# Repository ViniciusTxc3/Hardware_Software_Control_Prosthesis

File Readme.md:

Trabalho desenvolvido no BioLab - UFU para o controle de uma prótese robótica. Nele consta o desenvolvimento do software de controle em um microcontrolador DSPIC em c/c++ e os design das placas de controle PCB.

# Esse trabalho teve a colaboração direta de:
* Vinicius Teixeira da Costa, 
* Professor Alcimar Barbosa Soares, 
* Eber Lawrence Gouveia, 
* Arthur Coeolho

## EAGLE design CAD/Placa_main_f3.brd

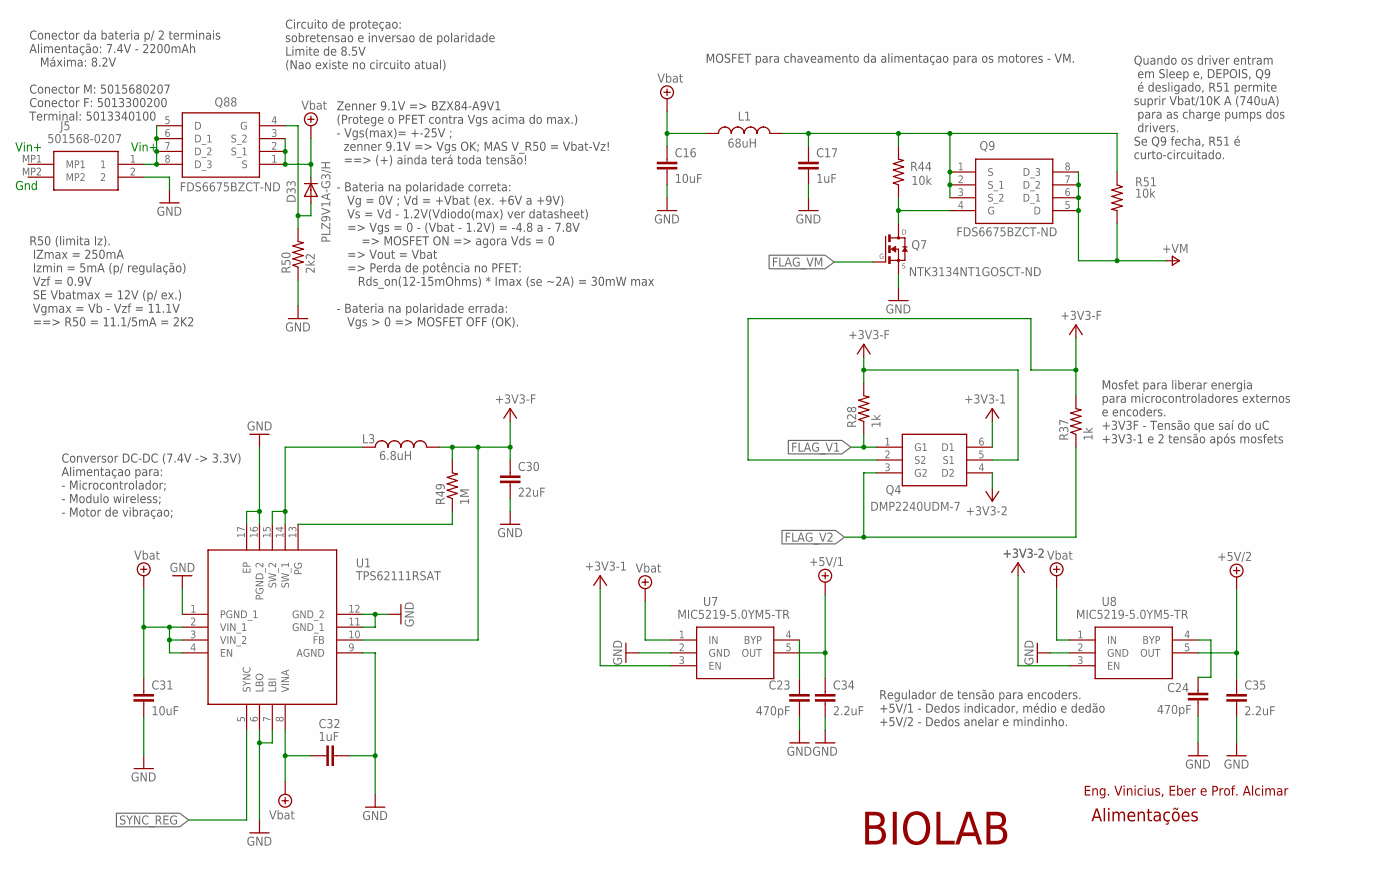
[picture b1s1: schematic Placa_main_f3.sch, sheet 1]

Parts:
C16, C31: 10uF; C0805K
C17, C32: 1uF; C0402K
C23, C24: 470pF; C0402K
C30: 22uF; C0805K
C34, C35: 2.2uF; C0402K
D33: PLZ9V1A-G3/H; MINIMELF
J5: 501568-0207; 5015680207
L1: 68uH; L2825P
L3: 6.8uH; L2825P
Q4: DMP2240UDM-7; SOT95P285X140-6N
Q7: NTK3134NT1GOSCT-ND; SOT23
Q9, Q88: FDS6675BZCT-ND; SOIC127P600X175-8N
R28, R37: 1k; R0402
R44, R51: 10k; R0402
R49: 1M; R0402
R50: 2k2; R0402
U1: TPS62111RSAT; QFN65P400X400X100-17N
U7, U8: MIC5219-5.0YM5-TR; SOT95P280X145-5N

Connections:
+3V3: C30.1, L3.2, Q4.2 (S2), Q4.5 (S1), R28.2, R37.2, R49.2, U1.10 (FB), U7.3 (EN); also elsewhere on the board
+3V3-1: Q4.6 (D1); also elsewhere on the board
+3V3-2: Q4.4 (D2), U8.3 (EN); also elsewhere on the board
+5V/1: C34.1, U7.5 (OUT); also elsewhere on the board
+5V/2: C35.1, U8.5 (OUT); also elsewhere on the board
FLAG_V1: Q4.1 (G1), R28.1; also elsewhere on the board
FLAG_V2: Q4.3 (G2), R37.1; also elsewhere on the board
FLAG_VM: Q7.1 (G); also elsewhere on the board
GND: C16.2, C17.2, C23.2, C24.2, C30.2, C31.2, C32.2, C34.2, C35.2, J5.2, Q7.2 (S), R50.1, U1.1 (PGND_1), U1.6 (LBO), U1.7 (LBI), U1.9 (AGND), U1.11 (GND_1), U1.12 (GND_2), U1.16 (PGND_2), U1.17 (EP), U7.2 (GND), U8.2 (GND); also elsewhere on the board
unnamed: C17.1, L1.2, Q9.1 (S), Q9.2 (S_1), Q9.3 (S_2), R44.2, R51.1
unnamed: Q7.3 (D), Q9.4 (G), R44.1
unnamed: C24.1, U8.4 (BYP)
unnamed: C23.1, U7.4 (BYP)
unnamed: R49.1, U1.13 (PG)
unnamed: L3.1, U1.14 (SW_1), U1.15 (SW_2)
unnamed: D33.A, Q88.4 (G), R50.2
SYNC_REG: U1.5 (SYNC); also elsewhere on the board
V+: Q9.5 (D), Q9.6 (D_1), Q9.7 (D_2), Q9.8 (D_3), R51.2; also elsewhere on the board
VBAT: C16.1, C31.1, C32.1, D33.C, L1.1, Q88.1 (S), Q88.2 (S_1), Q88.3 (S_2), U1.2 (VIN_1), U1.3 (VIN_2), U1.4 (EN), U1.8 (VINA), U7.1 (IN), U8.1 (IN); also elsewhere on the board
VIN+: J5.1, Q88.5 (D), Q88.6 (D_1), Q88.7 (D_2), Q88.8 (D_3)

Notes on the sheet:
Conector da bateria p/ 2 terminais Alimentação: 7.4V - 2200mAh Máxima: 8.2V Conector M: 5015680207 Conector F: 5013300200 Terminal: 5013340100
Circuito de proteçao: sobretensao e inversao de polaridade Limite de 8.5V (Nao existe no circuito atual)
Conversor DC-DC (7.4V -> 3.3V) Alimentaçao para: - Microcontrolador; - Modulo wireless; - Motor de vibraçao;
Regulador de tensão para encoders. +5V/1 - Dedos indicador, médio e dedão +5V/2 - Dedos anelar e mindinho.
MOSFET para chaveamento da alimentaçao para os motores - VM.
BIOLAB
Eng. Vinicius, Eber e Prof. Alcimar
Mosfet para liberar energia para microcontroladores externos e encoders. +3V3F - Tensão que saí do uC +3V3-1 e 2 tensão após mosfets
Alimentações
R50 (limita Iz). IZmax = 250mA Izmin = 5mA (p/ regulação) Vzf = 0.9V SE Vbatmax = 12V (p/ ex.) Vgmax = Vb - Vzf = 11.1V ==> R50 = 11.1/5mA = 2K2
Zenner 9.1V => BZX84-A9V1 (Protege o PFET contra Vgs acima do max.) - Vgs(max)= +-25V ; zenner 9.1V => Vgs OK; MAS V_R50 = Vbat-Vz! ==> (+) ainda terá toda tensão! - Bateria na polaridade correta: Vg = 0V ; Vd = +Vbat (ex. +6V a +9V) Vs = Vd - 1.2V(Vdiodo(max) ver datasheet) => Vgs = 0 - (Vbat - 1.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
Quando os driver entram em Sleep e, DEPOIS, Q9 é desligado, R51 permite suprir Vbat/10K A (740uA) para as charge pumps dos drivers. Se Q9 fecha, R51 é curto-circuitado.
Vin+
Gnd

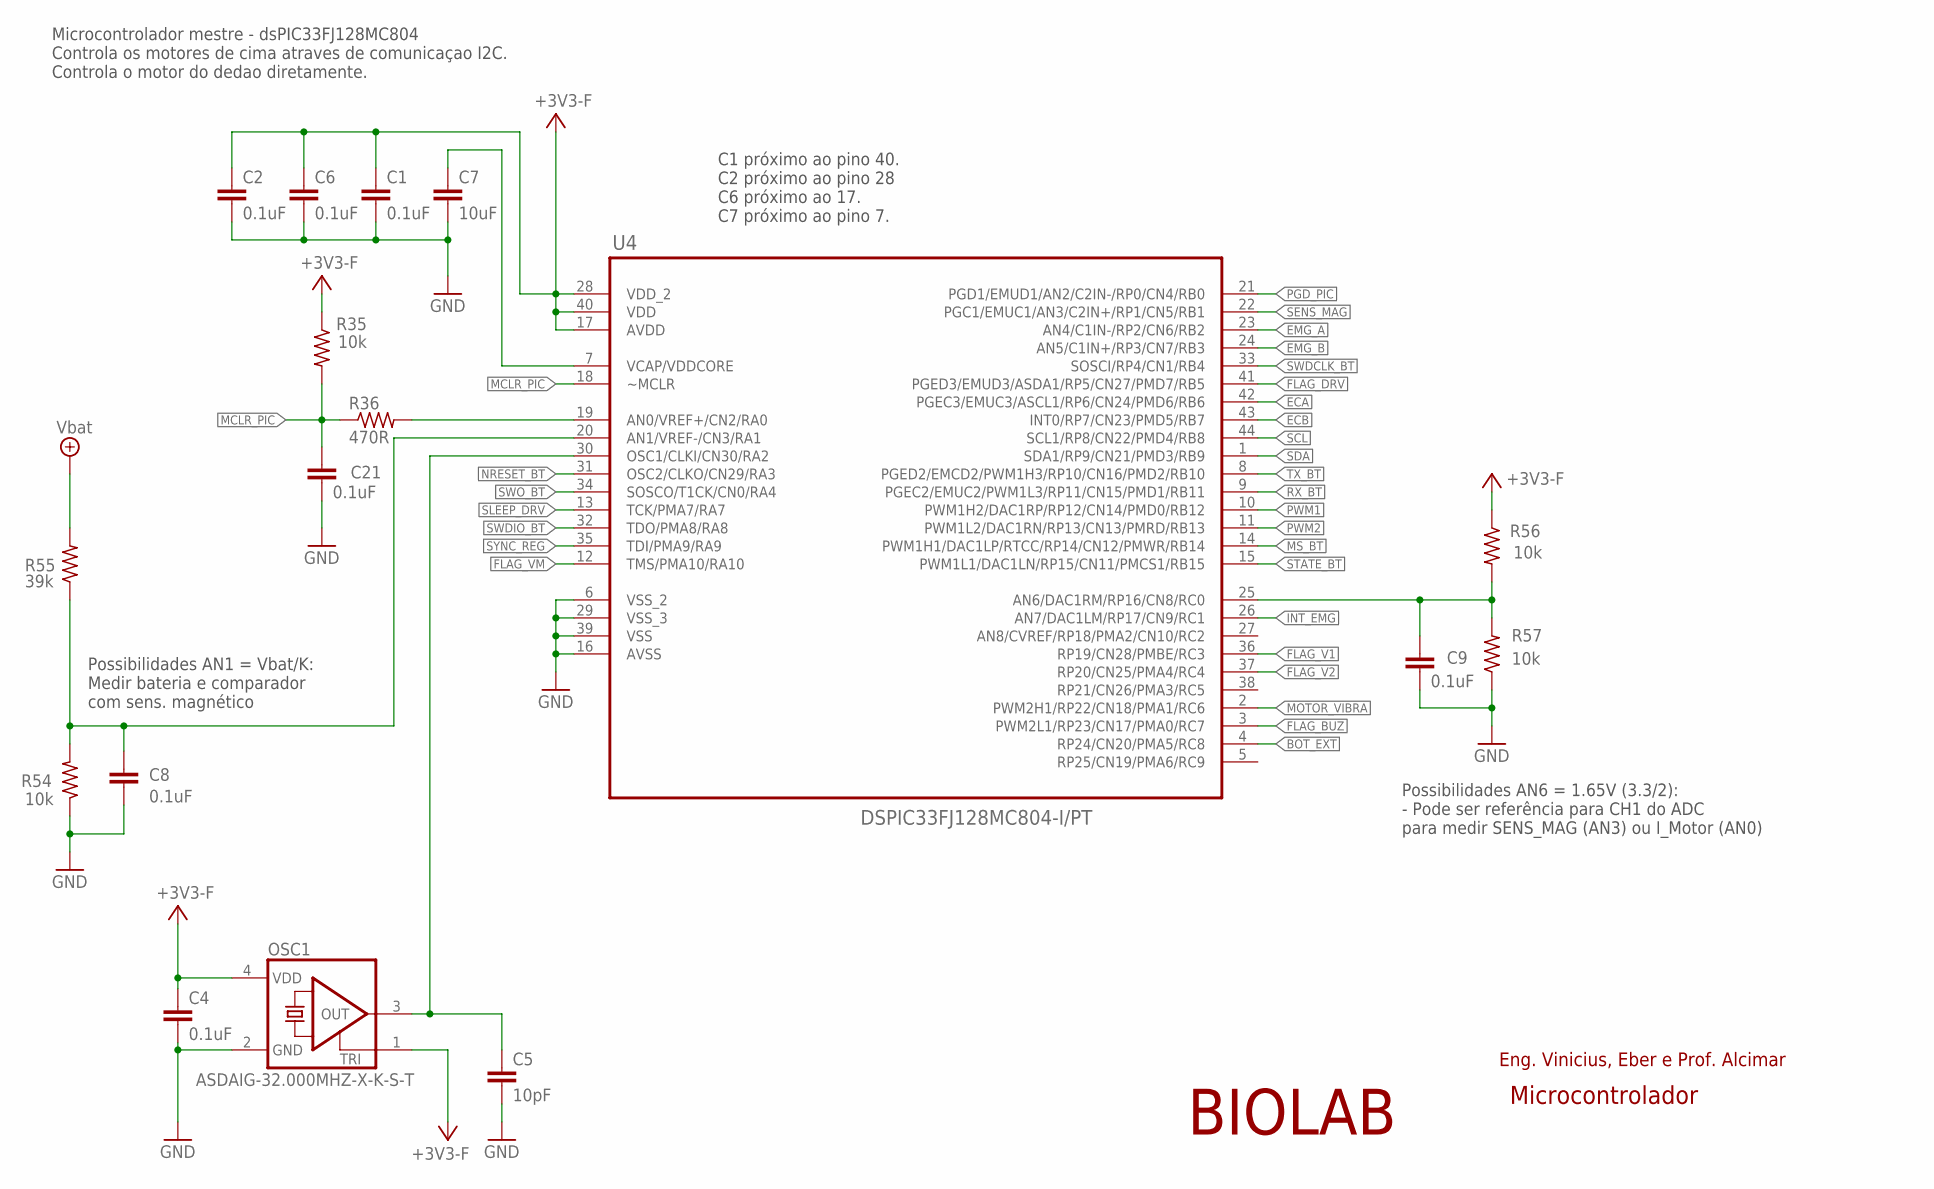
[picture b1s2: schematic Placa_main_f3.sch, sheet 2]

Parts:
C1, C2, C4, C6, C8, C9, C21: 0.1uF; C0402K
C5: 10pF; C0402K
C7: 10uF; C0805K
OSC1: ASDAIG-32.000MHZ-X-K-S-T; ASE
R35, R54, R56, R57: 10k; R0402
R36: 470R; R0402
R55: 39k; R0402
U4: DSPIC33FJ128MC804-I/PT; QFP80P1200X1200X120-44N

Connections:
+3V3: C1.1, C2.1, C4.1, C6.1, OSC1.1 (TRI), OSC1.4 (VDD), R35.1, R56.1, U4.17 (AVDD), U4.28 (VDD_2), U4.40 (VDD); also elsewhere on the board
BOT_EXT: U4.4 (RP24/CN20/PMA5/RC8); also elsewhere on the board
ECA: U4.42 (PGEC3/EMUC3/ASCL1/RP6/CN24/PMD6/RB6); also elsewhere on the board
ECB: U4.43 (INT0/RP7/CN23/PMD5/RB7); also elsewhere on the board
EMG_A: U4.23 (AN4/C1IN-/RP2/CN6/RB2); also elsewhere on the board
EMG_B: U4.24 (AN5/C1IN+/RP3/CN7/RB3); also elsewhere on the board
FLAG_BUZ: U4.3 (PWM2L1/RP23/CN17/PMA0/RC7); also elsewhere on the board
FLAG_DRV: U4.41 (PGED3/EMUD3/ASDA1/RP5/CN27/PMD7/RB5); also elsewhere on the board
FLAG_V1: U4.36 (RP19/CN28/PMBE/RC3); also elsewhere on the board
FLAG_V2: U4.37 (RP20/CN25/PMA4/RC4); also elsewhere on the board
FLAG_VM: U4.12 (TMS/PMA10/RA10); also elsewhere on the board
GND: C1.2, C2.2, C4.2, C5.2, C6.2, C7.2, C8.2, C9.2, C21.2, OSC1.2 (GND), R54.1, R57.1, U4.6 (VSS_2), U4.16 (AVSS), U4.29 (VSS_3), U4.39 (VSS); also elsewhere on the board
INT_EMG: U4.26 (AN7/DAC1LM/RP17/CN9/RC1); also elsewhere on the board
MCLR_PIC: C21.1, R35.2, R36.1, U4.18 (~MCLR); also elsewhere on the board
MOTOR_VIBRA: U4.2 (PWM2H1/RP22/CN18/PMA1/RC6); also elsewhere on the board
MS_BT: U4.14 (PWM1H1/DAC1LP/RTCC/RP14/CN12/PMWR/RB14); also elsewhere on the board
unnamed: C7.1, U4.7 (VCAP/VDDCORE)
unnamed: C9.1, R56.2, R57.2, U4.25 (AN6/DAC1RM/RP16/CN8/RC0)
unnamed: C8.1, R54.2, R55.1, U4.20 (AN1/VREF-/CN3/RA1)
unnamed: C5.1, OSC1.3 (OUT), U4.30 (OSC1/CLKI/CN30/RA2)
unnamed: R36.2, U4.19 (AN0/VREF+/CN2/RA0)
NRESET_BT: U4.31 (OSC2/CLKO/CN29/RA3); also elsewhere on the board
PGD_PIC: U4.21 (PGD1/EMUD1/AN2/C2IN-/RP0/CN4/RB0); also elsewhere on the board
PWM1: U4.10 (PWM1H2/DAC1RP/RP12/CN14/PMD0/RB12); also elsewhere on the board
PWM2: U4.11 (PWM1L2/DAC1RN/RP13/CN13/PMRD/RB13); also elsewhere on the board
RX_BT: U4.9 (PGEC2/EMUC2/PWM1L3/RP11/CN15/PMD1/RB11); also elsewhere on the board
SCL: U4.44 (SCL1/RP8/CN22/PMD4/RB8); also elsewhere on the board
SDA: U4.1 (SDA1/RP9/CN21/PMD3/RB9); also elsewhere on the board
SENS_MAG: U4.22 (PGC1/EMUC1/AN3/C2IN+/RP1/CN5/RB1); also elsewhere on the board
SLEEP_DRV: U4.13 (TCK/PMA7/RA7); also elsewhere on the board
STATE_BT: U4.15 (PWM1L1/DAC1LN/RP15/CN11/PMCS1/RB15); also elsewhere on the board
SWDCLK_BT: U4.33 (SOSCI/RP4/CN1/RB4); also elsewhere on the board
SWDIO_BT: U4.32 (TDO/PMA8/RA8); also elsewhere on the board
SWO_BT: U4.34 (SOSCO/T1CK/CN0/RA4); also elsewhere on the board
SYNC_REG: U4.35 (TDI/PMA9/RA9); also elsewhere on the board
TX_BT: U4.8 (PGED2/EMCD2/PWM1H3/RP10/CN16/PMD2/RB10); also elsewhere on the board
VBAT: R55.2; also elsewhere on the board

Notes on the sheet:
Microcontrolador mestre - dsPIC33FJ128MC804 Controla os motores de cima atraves de comunicaçao I2C. Controla o motor do dedao diretamente.
BIOLAB
Eng. Vinicius, Eber e Prof. Alcimar
Microcontrolador
C1 próximo ao pino 40. C2 próximo ao pino 28 C6 próximo ao 17. C7 próximo ao pino 7.
Possibilidades AN6 = 1.65V (3.3/2): - Pode ser referência para CH1 do ADC para medir SENS_MAG (AN3) ou I_Motor (AN0)
Possibilidades AN1 = Vbat/K: Medir bateria e comparador com sens. magnético

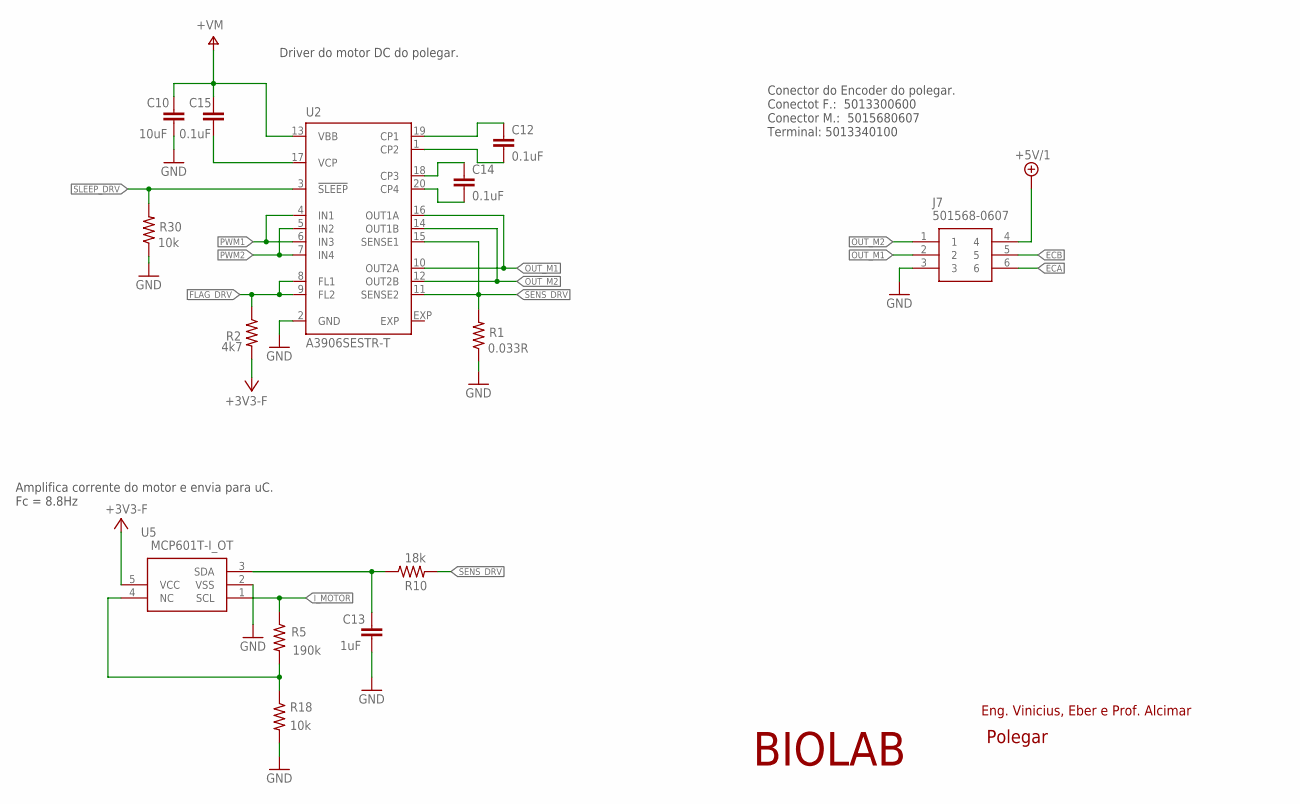
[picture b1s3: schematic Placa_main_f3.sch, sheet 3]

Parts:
C10: 10uF; C0805K
C12, C14, C15: 0.1uF; C0402K
C13: 1uF; C0402K
J7: 501568-0607
R1: 0.033R; R0805
R2: 4k7; R0402
R5: 190k; R0402
R10: 18k; R0402
R18, R30: 10k; R0402
U2: A3906SESTR-T; QFN20
U5: MCP601T-I_OT; SOT95P270X145-5N

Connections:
+3V3: R2.2, U5.5 (VCC); also elsewhere on the board
+5V/1: J7.4; also elsewhere on the board
ECA: J7.6; also elsewhere on the board
ECB: J7.5; also elsewhere on the board
FLAG_DRV: R2.1, U2.8 (FL1), U2.9 (FL2); also elsewhere on the board
GND: C10.1, C13.2, J7.3, R1.1, R18.2, R30.1, U2.2 (GND), U5.2 (VSS); also elsewhere on the board
I_MOTOR: R5.1, U5.1 (SCL)
unnamed: C13.1, R10.1, U5.3 (SDA)
unnamed: C12.2, U2.1 (CP2)
unnamed: C14.1, U2.18 (CP3)
unnamed: C15.2, U2.17 (VCP)
unnamed: C14.2, U2.20 (CP4)
unnamed: C12.1, U2.19 (CP1)
unnamed: R5.2, R18.1, U5.4 (NC)
OUT_M1: J7.2, U2.10 (OUT2A), U2.16 (OUT1A)
OUT_M2: J7.1, U2.12 (OUT2B), U2.14 (OUT1B)
PWM1: U2.4 (IN1), U2.6 (IN3); also elsewhere on the board
PWM2: U2.5 (IN2), U2.7 (IN4); also elsewhere on the board
SENS_DRV: R1.2, R10.2, U2.11 (SENSE2), U2.15 (SENSE1)
SLEEP_DRV: R30.2, U2.3 (!SLEEP); also elsewhere on the board
V+: C10.2, C15.1, U2.13 (VBB); also elsewhere on the board

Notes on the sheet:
Driver do motor DC do polegar.
Conector do Encoder do polegar. Conectot F.: 5013300600 Conector M.: 5015680607 Terminal: 5013340100
Amplifica corrente do motor e envia para uC. Fc = 8.8Hz
BIOLAB
Eng. Vinicius, Eber e Prof. Alcimar
Polegar

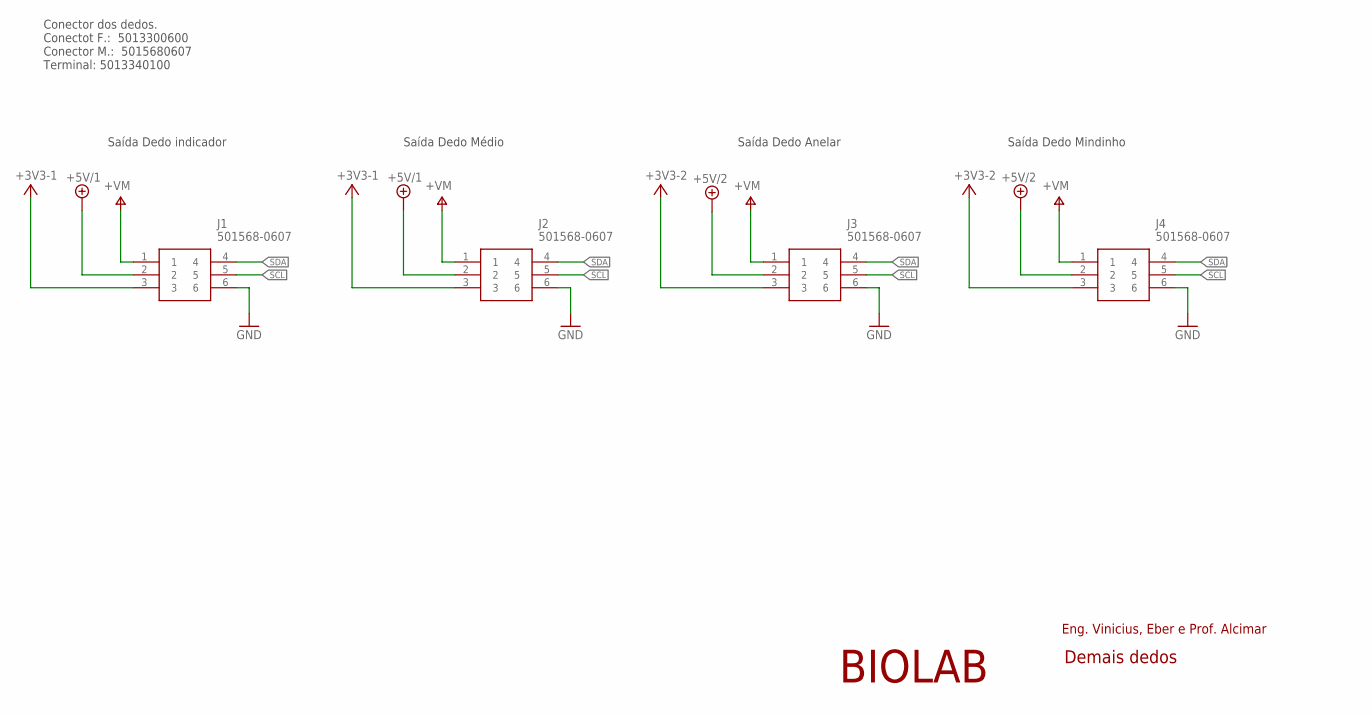
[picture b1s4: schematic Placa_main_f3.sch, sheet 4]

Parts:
J1, J2, J3, J4: 501568-0607

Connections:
+3V3-1: J1.3, J2.3; also elsewhere on the board
+3V3-2: J3.3, J4.3; also elsewhere on the board
+5V/1: J1.2, J2.2; also elsewhere on the board
+5V/2: J3.2, J4.2; also elsewhere on the board
GND: J1.6, J2.6, J3.6, J4.6; also elsewhere on the board
SCL: J1.5, J2.5, J3.5, J4.5; also elsewhere on the board
SDA: J1.4, J2.4, J3.4, J4.4; also elsewhere on the board
V+: J1.1, J2.1, J3.1, J4.1; also elsewhere on the board

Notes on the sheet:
BIOLAB
Eng. Vinicius, Eber e Prof. Alcimar
Demais dedos
Conector dos dedos. Conectot F.: 5013300600 Conector M.: 5015680607 Terminal: 5013340100
Saída Dedo indicador
Saída Dedo Médio
Saída Dedo Anelar
Saída Dedo Mindinho

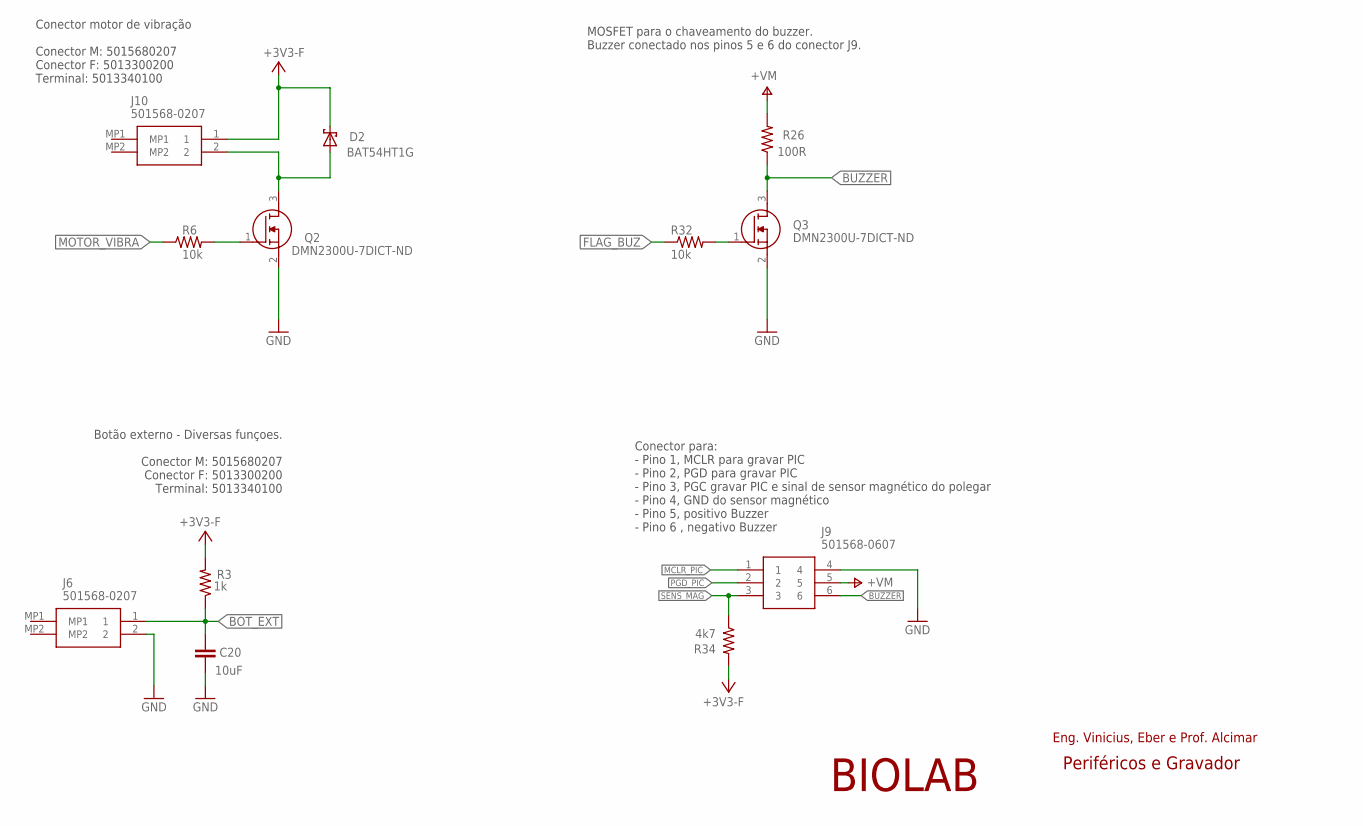
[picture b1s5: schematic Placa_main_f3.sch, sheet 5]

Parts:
C20: 10uF; C0402K
D2: BAT54HT1G; SOT23
J6, J10: 501568-0207; 5015680207
J9: 501568-0607
Q2, Q3: DMN2300U-7DICT-ND; SOT96P240X110-3N
R3: 1k; R0402
R6, R32: 10k; R0402
R26: 100R; R0402
R34: 4k7; R0402

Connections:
+3V3: D2.3 (C), J10.1, R3.2, R34.2; also elsewhere on the board
BOT_EXT: C20.1, J6.1, R3.1; also elsewhere on the board
BUZZER: J9.6, Q3.3 (D), R26.1
FLAG_BUZ: R32.1; also elsewhere on the board
GND: C20.2, J6.2, J9.4, Q2.2 (S), Q3.2 (S); also elsewhere on the board
MCLR_PIC: J9.1; also elsewhere on the board
MOTOR_VIBRA: R6.1; also elsewhere on the board
unnamed: Q2.1 (G), R6.2
unnamed: D2.1 (A), J10.2, Q2.3 (D)
unnamed: Q3.1 (G), R32.2
PGD_PIC: J9.2; also elsewhere on the board
SENS_MAG: J9.3, R34.1; also elsewhere on the board
V+: J9.5, R26.2; also elsewhere on the board

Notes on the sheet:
Botão externo - Diversas funçoes. Conector M: 5015680207 Conector F: 5013300200 Terminal: 5013340100
Conector para: - Pino 1, MCLR para gravar PIC - Pino 2, PGD para gravar PIC - Pino 3, PGC gravar PIC e sinal de sensor magnético do polegar - Pino 4, GND do sensor magnético - Pino 5, positivo Buzzer - Pino 6 , negativo Buzzer
MOSFET para o chaveamento do buzzer. Buzzer conectado nos pinos 5 e 6 do conector J9.
BIOLAB
Eng. Vinicius, Eber e Prof. Alcimar
Periféricos e Gravador
Conector motor de vibração Conector M: 5015680207 Conector F: 5013300200 Terminal: 5013340100

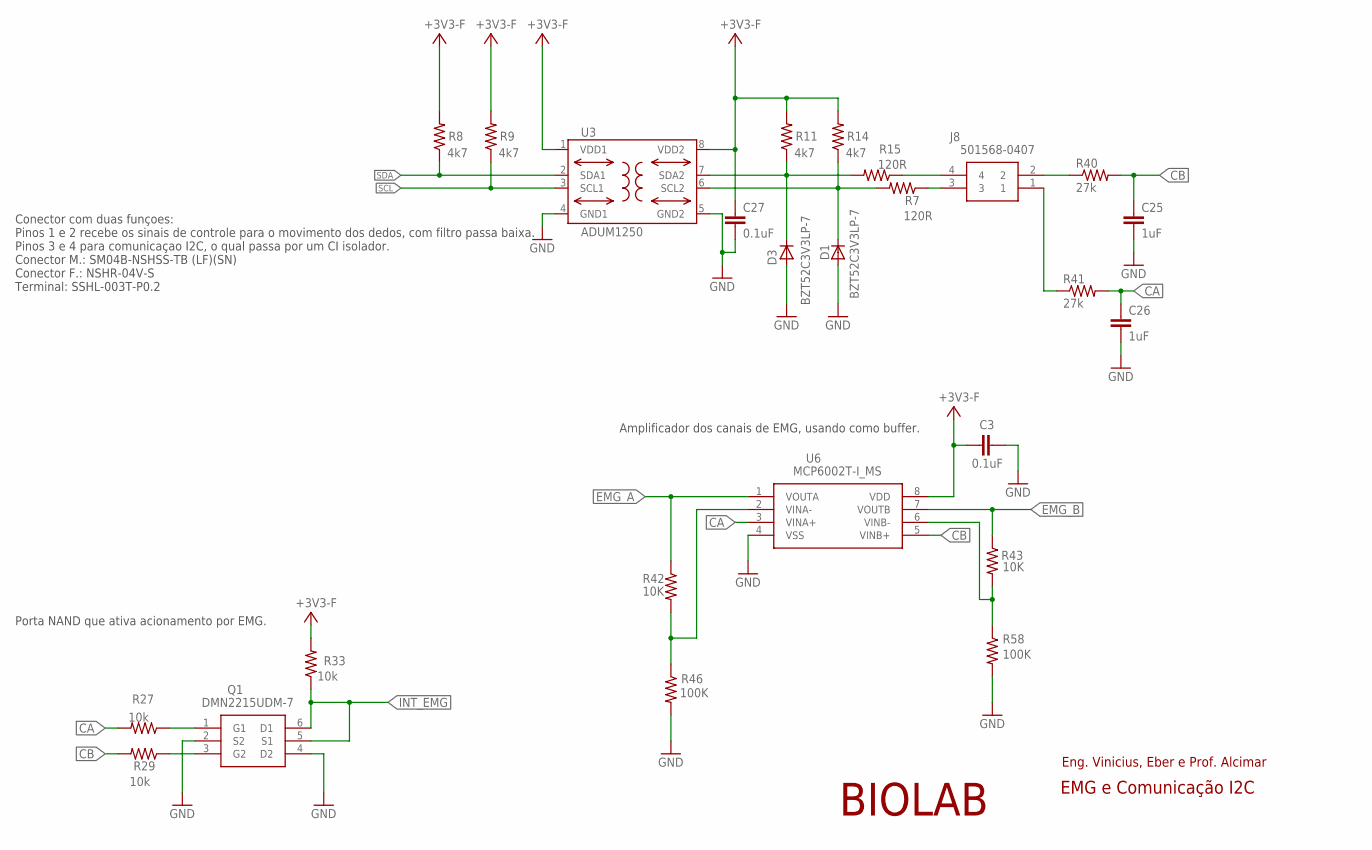
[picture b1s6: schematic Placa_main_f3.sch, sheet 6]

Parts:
C3, C27: 0.1uF; C0402K
C25, C26: 1uF; C0402K
D1, D3: BZT52C3V3LP-7; MINIMELF
J8: 501568-0407
Q1: DMN2215UDM-7; SOT95P285X140-6N
R7, R15: 120R; R0402
R8, R9, R11, R14: 4k7; R0402
R27, R29, R33: 10k; R0402
R40, R41: 27k; R0402
R42, R43: 10K; R0402
R46, R58: 100K; R0402
U3: ADUM1250; SO8-COOL
U6: MCP6002T-I_MS; SOP65P490X110-8N

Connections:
+3V3: C3.1, C27.1, R8.2, R9.2, R11.2, R14.2, R33.2, U3.1 (VDD1), U3.8 (VDD2), U6.8 (VDD); also elsewhere on the board
CA: C26.1, R27.2, R41.2, U6.3 (VINA+)
CB: C25.1, R29.2, R40.2, U6.5 (VINB+)
EMG_A: R42.1, U6.1 (VOUTA); also elsewhere on the board
EMG_B: R43.1, U6.7 (VOUTB); also elsewhere on the board
GND: C3.2, C25.2, C26.2, C27.2, D1.A, D3.A, Q1.2 (S2), Q1.4 (D2), R46.2, R58.2, U3.4 (GND1), U3.5 (GND2), U6.4 (VSS); also elsewhere on the board
INT_EMG: Q1.5 (S1), Q1.6 (D1), R33.1; also elsewhere on the board
unnamed: J8.3, R7.1
unnamed: D3.C, R11.1, R15.2, U3.7 (SDA2)
unnamed: Q1.1 (G1), R27.1
unnamed: Q1.3 (G2), R29.1
unnamed: J8.4, R15.1
unnamed: R42.2, R46.1, U6.2 (VINA-)
unnamed: R43.2, R58.1, U6.6 (VINB-)
unnamed: D1.C, R7.2, R14.1, U3.6 (SCL2)
unnamed: J8.2, R40.1
unnamed: J8.1, R41.1
SCL: R9.1, U3.3 (SCL1); also elsewhere on the board
SDA: R8.1, U3.2 (SDA1); also elsewhere on the board

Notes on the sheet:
BIOLAB
Eng. Vinicius, Eber e Prof. Alcimar
Conector com duas funçoes: Pinos 1 e 2 recebe os sinais de controle para o movimento dos dedos, com filtro passa baixa. Pinos 3 e 4 para comunicaçao I2C, o qual passa por um CI isolador. Conector M.: SM04B-NSHSS-TB (LF)(SN) Conector F.: NSHR-04V-S Terminal: SSHL-003T-P0.2
EMG e Comunicação I2C
Porta NAND que ativa acionamento por EMG.
Amplificador dos canais de EMG, usando como buffer.

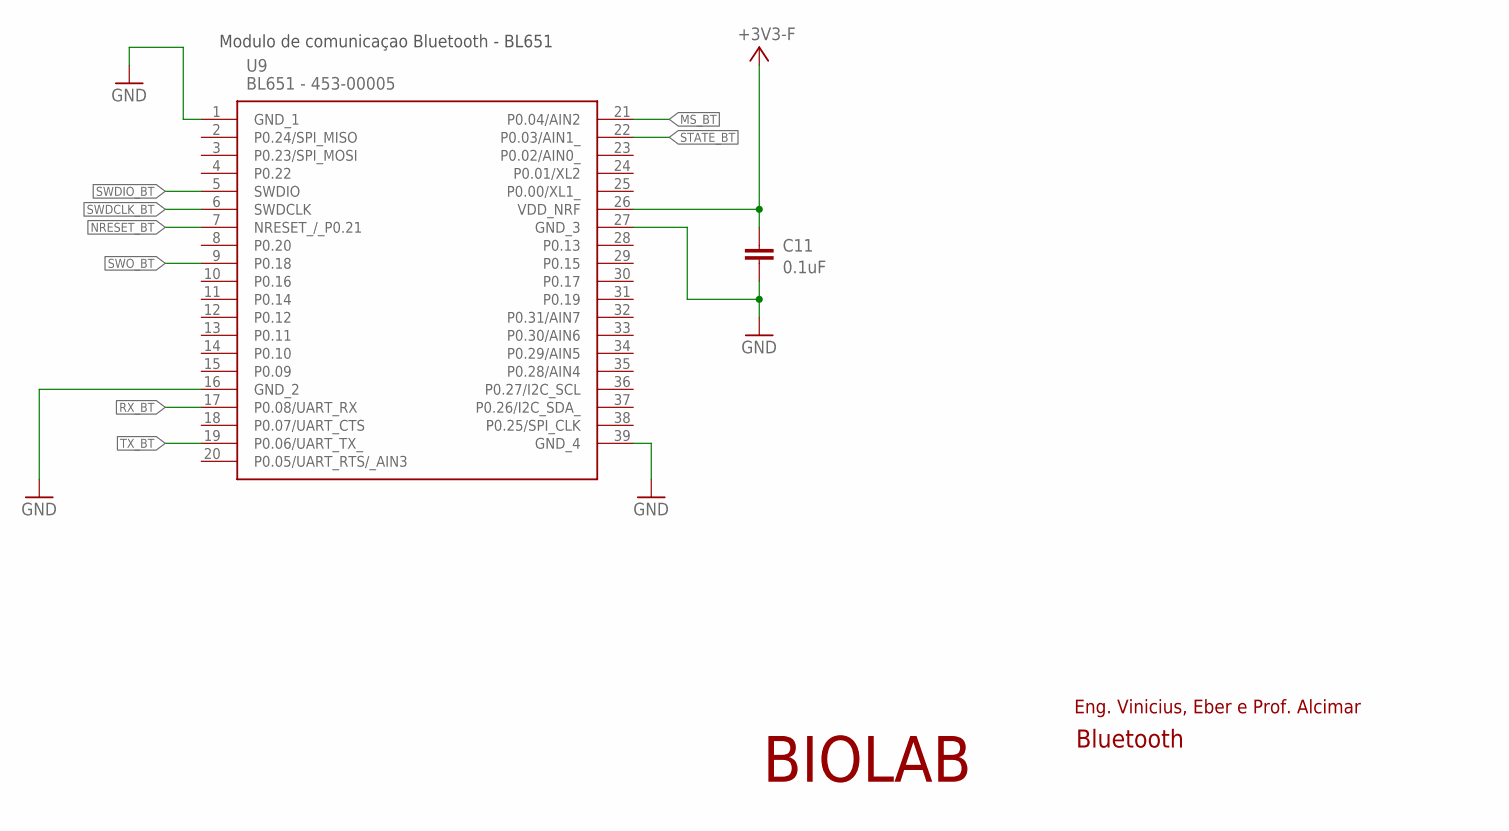
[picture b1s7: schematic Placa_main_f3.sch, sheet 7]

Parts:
C11: 0.1uF; C0402K
U9: BL651 - 453-00005; 45300005

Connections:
+3V3: C11.2, U9.26 (VDD_NRF); also elsewhere on the board
GND: C11.1, U9.1 (GND_1), U9.16 (GND_2), U9.27 (GND_3), U9.39 (GND_4); also elsewhere on the board
MS_BT: U9.21 (P0.04/AIN2); also elsewhere on the board
NRESET_BT: U9.7 (NRESET_/_P0.21); also elsewhere on the board
RX_BT: U9.17 (P0.08/UART_RX); also elsewhere on the board
STATE_BT: U9.22 (P0.03/AIN1_); also elsewhere on the board
SWDCLK_BT: U9.6 (SWDCLK); also elsewhere on the board
SWDIO_BT: U9.5 (SWDIO); also elsewhere on the board
SWO_BT: U9.9 (P0.18); also elsewhere on the board
TX_BT: U9.19 (P0.06/UART_TX_); also elsewhere on the board

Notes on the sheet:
Modulo de comunicaçao Bluetooth - BL651
BIOLAB
Eng. Vinicius, Eber e Prof. Alcimar
Bluetooth

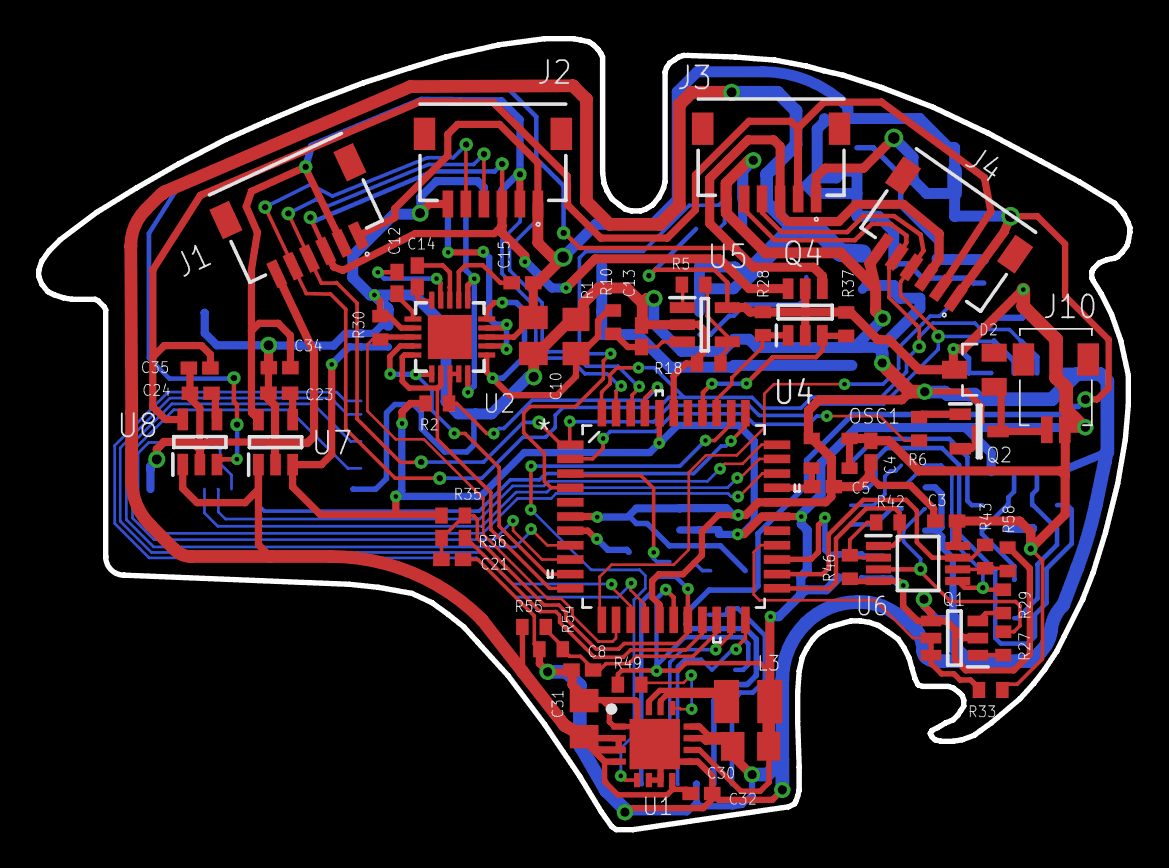
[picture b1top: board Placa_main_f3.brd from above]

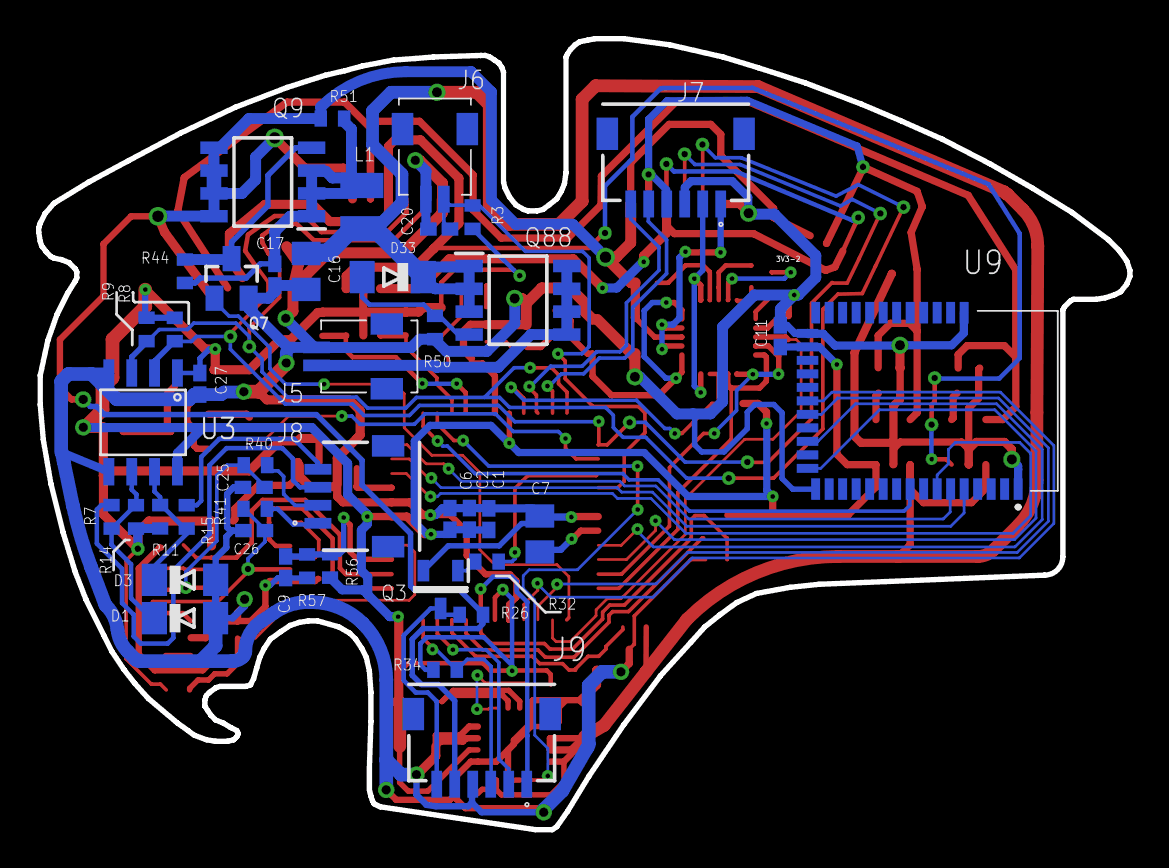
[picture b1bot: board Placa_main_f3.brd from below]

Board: 2 copper layers, 60.6 x 43.9 mm, 100 parts (44 on the bottom side), 77 nets.

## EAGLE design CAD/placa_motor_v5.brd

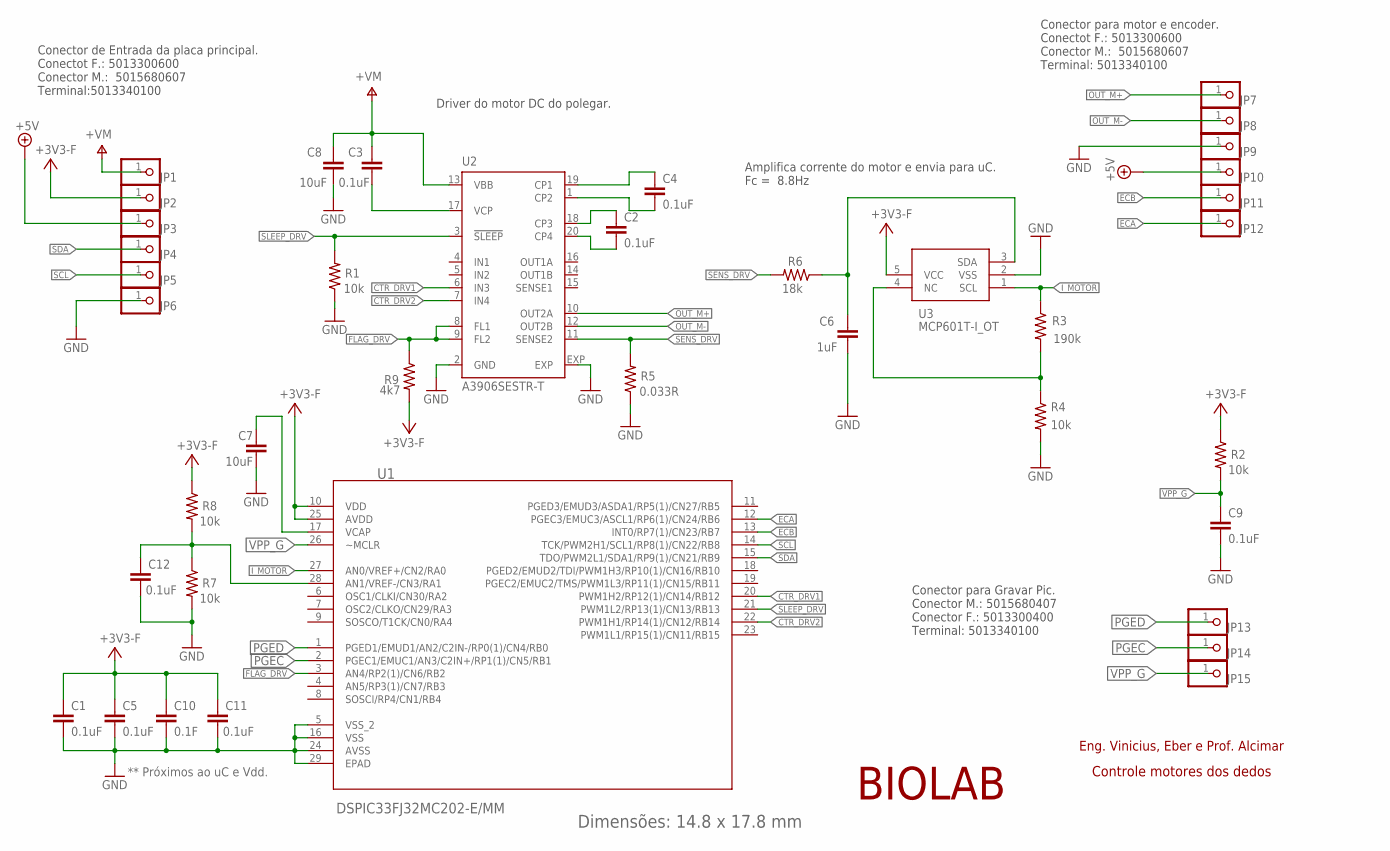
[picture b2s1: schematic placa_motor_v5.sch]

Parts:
C1, C2, C3, C4, C5, C9, C11, C12: 0.1uF; C0402K
C6: 1uF; C0402K
C7, C8: 10uF; C0805K
C10: 0.1F; C0402K
JP1, JP2, JP3, JP4, JP5, JP6, JP7, JP8, JP9, JP10, JP11, JP12, JP13, JP14, JP15: PINHD-1X1; 1X01
R1, R2, R4, R7, R8: 10k; R0402
R3: 190k; R0402
R5: 0.033R; R0805
R6: 18k; R0402
R9: 4k7; R0402
U1: DSPIC33FJ32MC202-E/MM; QFN65P600X600X100-29N
U2: A3906SESTR-T; QFN20
U3: MCP601T-I_OT; SOT95P270X145-5N

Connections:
+3V3: C1.1, C5.1, C10.1, C11.1, JP2.1, R2.1, R8.1, R9.2, U1.10 (VDD), U1.25 (AVDD), U3.5 (VCC)
+5V: JP3.1, JP10.1
AUX: C12.1, R7.1, R8.2, U1.28 (AN1/VREF-/CN3/RA1)
CTR_DRV1: U1.20 (PWM1H2/RP12(1)/CN14/RB12), U2.6 (IN3)
CTR_DRV2: U1.22 (PWM1H1/RP14(1)/CN12/RB14), U2.7 (IN4)
ECA: JP12.1, U1.12 (PGEC3/EMUC3/ASCL1/RP6(1)/CN24/RB6)
ECB: JP11.1, U1.13 (INT0/RP7(1)/CN23/RB7)
FLAG_DRV: R9.1, U1.3 (AN4/RP2(1)/CN6/RB2), U2.8 (FL1), U2.9 (FL2)
GND: C1.2, C5.2, C6.2, C7.2, C8.1, C9.2, C10.2, C11.2, C12.2, JP6.1, JP9.1, R1.1, R4.2, R5.1, R7.2, U1.5 (VSS_2), U1.16 (VSS), U1.24 (AVSS), U1.29 (EPAD), U2.2 (GND), U2.EXP, U3.2 (VSS)
I_MOTOR: R3.1, U1.27 (AN0/VREF+/CN2/RA0), U3.1 (SCL)
N1: C7.1, U1.17 (VCAP)
N2: R3.2, R4.1, U3.4 (NC)
N3: C6.1, R6.1, U3.3 (SDA)
N4: C4.1, U2.19 (CP1)
N5: C4.2, U2.1 (CP2)
N6: C2.1, U2.18 (CP3)
N7: C2.2, U2.20 (CP4)
N8: C3.2, U2.17 (VCP)
OUT_M+: JP7.1, U2.10 (OUT2A)
OUT_M-: JP8.1, U2.12 (OUT2B)
PGEC: JP14.1, U1.2 (PGEC1/EMUC1/AN3/C2IN+/RP1(1)/CN5/RB1)
PGED: JP13.1, U1.1 (PGED1/EMUD1/AN2/C2IN-/RP0(1)/CN4/RB0)
SCL: JP5.1, U1.14 (TCK/PWM2H1/SCL1/RP8(1)/CN22/RB8)
SDA: JP4.1, U1.15 (TDO/PWM2L1/SDA1/RP9(1)/CN21/RB9)
SENS_DRV: R5.2, R6.2, U2.11 (SENSE2)
SLEEP_DRV: R1.2, U1.21 (PWM1L2/RP13(1)/CN13/RB13), U2.3 (!SLEEP)
V+: C3.1, C8.2, JP1.1, U2.13 (VBB)
VPP_G: C9.1, JP15.1, R2.2, U1.26 (~MCLR)

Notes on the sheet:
Dimensões: 14.8 x 17.8 mm
** Próximos ao uC e Vdd.
Conector para motor e encoder. Conectot F.: 5013300600 Conector M.: 5015680607 Terminal: 5013340100
Conector de Entrada da placa principal. Conectot F.: 5013300600 Conector M.: 5015680607 Terminal:5013340100
BIOLAB
Eng. Vinicius, Eber e Prof. Alcimar
Driver do motor DC do polegar.
Amplifica corrente do motor e envia para uC. Fc = 8.8Hz
Controle motores dos dedos
Conector para Gravar Pic. Conector M.: 5015680407 Conector F.: 5013300400 Terminal: 5013340100

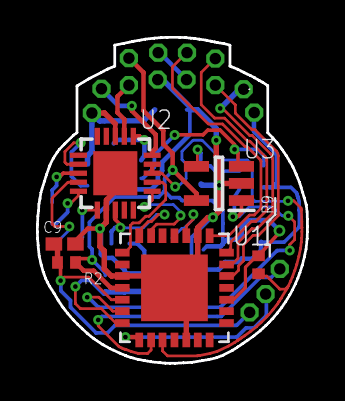
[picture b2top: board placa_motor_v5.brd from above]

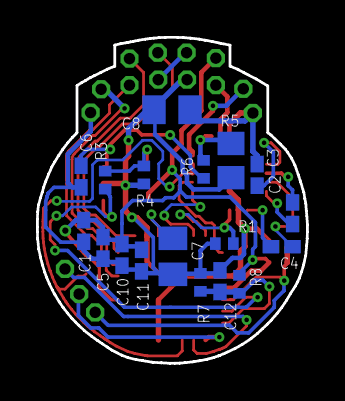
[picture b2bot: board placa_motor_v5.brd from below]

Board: 2 copper layers, 15.0 x 18.1 mm, 39 parts (18 on the bottom side), 28 nets.

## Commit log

2022-04-04 Projeto finalizado
2022-04-04 Arrumando readme
